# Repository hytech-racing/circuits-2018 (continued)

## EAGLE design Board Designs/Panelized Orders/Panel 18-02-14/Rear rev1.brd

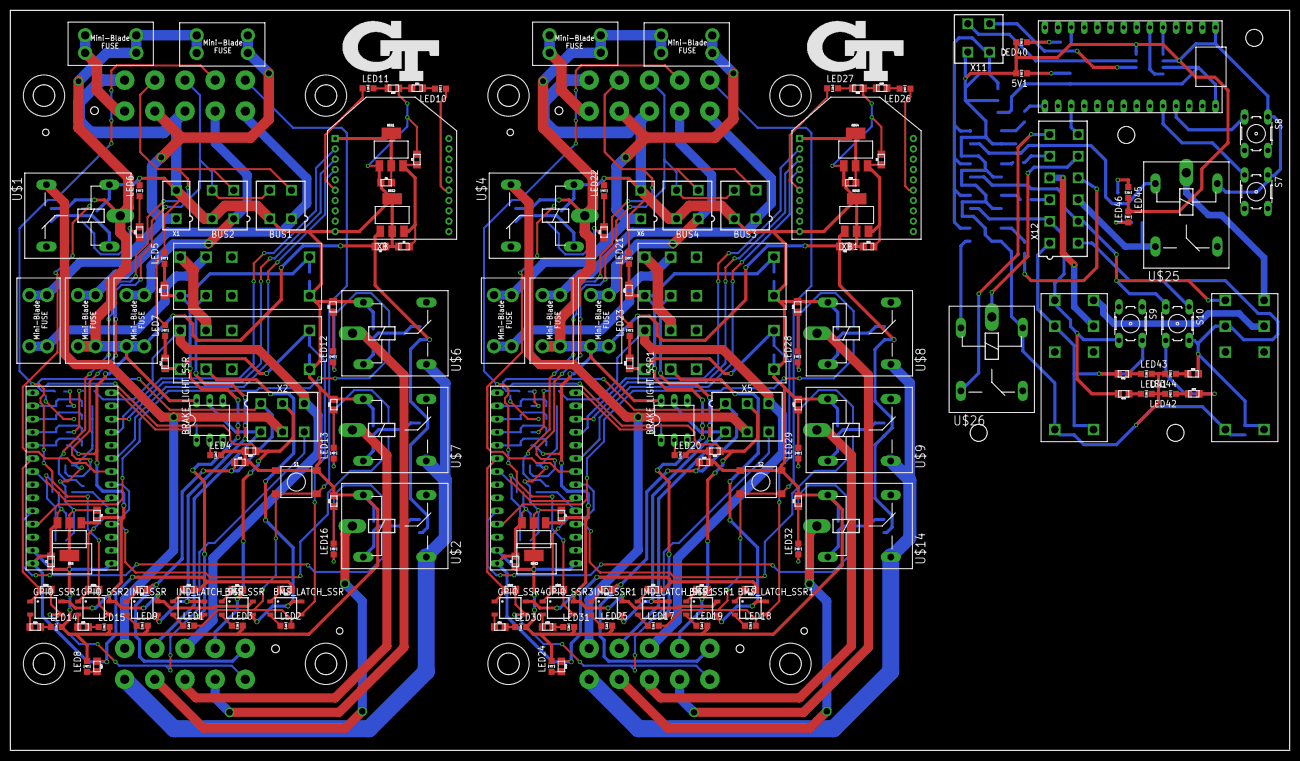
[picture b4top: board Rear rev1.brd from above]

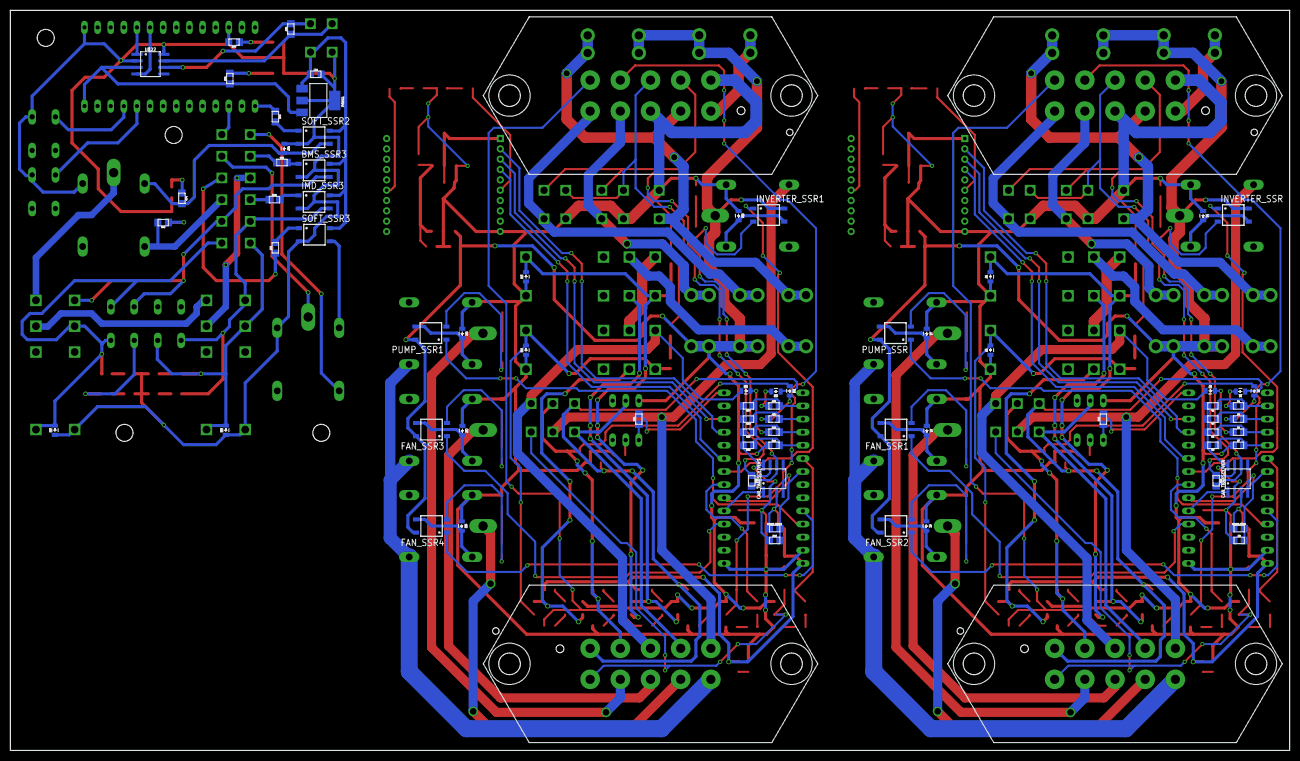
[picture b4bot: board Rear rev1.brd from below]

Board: 2 copper layers, 247.7 x 143.3 mm, 236 parts (75 on the bottom side), 203 nets.

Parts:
5V1: LED-805
5VREG1: SOT223
BMS_LATCH_SSR, BMS_LATCH_SSR1: CPC1002N; SOP04
BMS_SSR, BMS_SSR1, BMS_SSR3: CPC1002N; SOP04
BOARD_TEMP, BOARD_TEMP1: THERMISTOR_NCP210805; 0805
BRAKE_LIGHT_SSR, BRAKE_LIGHT_SSR1: SOLID_STATE_RELAY_VO14642AT; DIL06
BUS1, BUS2, BUS3, BUS4: CONNECTOR-4; MINIFIT_5566-4
C1, C5, C7, C11, C14: .22uF; 0805
C2, C6, C8, C12: .1uF; 0805
C3, C4, C9, C10: 1uF; 0805
CAN_TRANSCEIVER, CAN_TRANSCEIVER1: MCP2551; SOIC-08
D1, D2, D3, D4, D5, D6, D7, D8, D9, D10, D11, D12, D13, D14, D15, D16, D17, D18, D22, D23, D24: DIODE0805; 0805_D
FAN_SSR1, FAN_SSR2, FAN_SSR3, FAN_SSR4: CPC1002N; SOP04
FH_FUSE, FH_FUSE1: 8A; MINI-BLADE_FUSE_HOLDER
FSAE_FUSE, FSAE_FUSE1: 8A; MINI-BLADE_FUSE_HOLDER
FUSE_BUS_1, FUSE_BUS_2, FUSE_BUS_3, FUSE_BUS_4: 5A; MINI-BLADE_FUSE_HOLDER
GPIO_SSR1, GPIO_SSR2, GPIO_SSR3, GPIO_SSR4: CPC1002N; SOP04
IMD_LATCH_SSR, IMD_LATCH_SSR1: CPC1002N; SOP04
IMD_SHUTDOWN, IMD_SHUTDOWN1, IMD_SHUTDOWN2, IMD_SHUTDOWN3: G2RL-2-DC12; G2RL-2
IMD_SSR, IMD_SSR1, IMD_SSR3: CPC1002N; SOP04
INVERTER_SSR, INVERTER_SSR1: CPC1002N; SOP04
LED1, LED2, LED17, LED18: White; LED-805
LED3, LED7, LED11, LED19, LED23, LED27: Green; LED-805
LED4, LED6, LED10, LED12, LED13, LED14, LED15, LED16, LED20, LED22, LED26, LED28, LED29, LED30, LED31, LED32: Red; LED-805
LED5, LED9, LED21, LED25: Yellow; LED-805
LED8, LED24: Purple; LED-805
LED40, LED41, LED42, LED43, LED44, LED45, LED46: LED-805
PUMP_SSR, PUMP_SSR1: CPC1002N; SOP04
R1, R3, R5, R7, R25, R37, R39, R41: 43k; 0805
R2, R4, R6, R8, R36, R38, R40, R42: 12k; 0805
R9, R19, R43, R46: 10k; 0805
R10, R11, R16, R26, R29, R30, R31, R44, R54, R55: 43; 0805
R12, R13, R23, R24, R27, R28, R32, R33, R51, R52, R53, R56: 33; 0805
R14, R17, R21, R34, R45, R49: 820; 0805
R15, R35, R78: 120; 0805
R18, R47: 2.2k; 0805
R20, R48: 270; 0805
R22, R50: 100; 0805
R70, R71, R72, R73, R74, R75, R76, R77, R79, R80, R81, R82: 0805
REG, REG2, REG3, REG5: 5V; SOT223
REG1, REG4: TLV1117LV33; SOT223
S1, S2: TACTILE_SWITCH_SMD_6.2MM_TALL
S7, S8, S9, S10: B3F-10XX
SHUTDWN_FUSE, SHUTDWN_FUSE1: 5A; MINI-BLADE_FUSE_HOLDER
SOFT_SSR2, SOFT_SSR3: CPC1002N; SOP04
U$1, U$2, U$4, U$6, U$7, U$8, U$9, U$14, U$25, U$26: G5LE; ZF112
U$3, U$5, U$21: TEENSY_3.2_SIMPLE
U$10, U$11, U$12, U$13: JUMPER; 0805
U$22: MCP2551; SOIC-08
U$23, U$24: G2RL-2-DC12; G2RL-2
X1, X6: CONNECTOR-2; MINIFIT_5566-2
X2, X5: CONNECTOR-6; MINIFIT_5566-6
X3, X4, X7, X8: CONNECTOR-10MX150L_VERTICAL-10; MX150L_VERTICAL-10
X11: CONNECTOR-4; MINIFIT_5566-4
X12: CONNECTOR-12; MINIFIT_5566-12
XB, XB1: XBEE

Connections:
12VSUPPLY_BRB: FH_FUSE.R1, FH_FUSE.R2, SHUTDWN_FUSE.R1, SHUTDWN_FUSE.R2, X1.1, X4.2
12VSUPPLY_BRB1: FH_FUSE1.R1, FH_FUSE1.R2, SHUTDWN_FUSE1.R1, SHUTDWN_FUSE1.R2, X6.1, X8.2
12VSUPPLY_FSAE: FSAE_FUSE.R1, FSAE_FUSE.R2, X4.1
12VSUPPLY_FSAE1: FSAE_FUSE1.R1, FSAE_FUSE1.R2, X8.1
12VSUPPLY_READ: R7.2, R8.1, U$3.A3
12VSUPPLY_READ1: R41.2, R42.1, U$5.A3
12V_F1: BUS1.1, FUSE_BUS_1.R1, FUSE_BUS_1.R2, X4.5
12V_F2: BUS2.1, FUSE_BUS_2.R1, FUSE_BUS_2.R2, X4.4
12V_F3: BUS3.1, FUSE_BUS_3.R1, FUSE_BUS_3.R2, X8.5
12V_F4: BUS4.1, FUSE_BUS_4.R1, FUSE_BUS_4.R2, X8.4
+5V: BOARD_TEMP.1, C2.2, CAN_TRANSCEIVER.3, R12.2, R13.1, R20.1, REG.3, U$3.VIN
+5V1: BOARD_TEMP1.1, C8.2, CAN_TRANSCEIVER1.3, R32.2, R33.1, R48.1, REG3.3, U$5.VIN
+5V3: 5VREG1.3, R71.1, U$21.VIN, U$22.3
+12V: BMS_SSR.4, BRAKE_LIGHT_SSR.6, C1.2, C5.2, FAN_SSR1.4, FAN_SSR2.4, FH_FUSE.L1, FH_FUSE.L2, FSAE_FUSE.L1, FSAE_FUSE.L2, FUSE_BUS_1.L1, FUSE_BUS_1.L2, FUSE_BUS_2.L1, FUSE_BUS_2.L2, GPIO_SSR1.4, GPIO_SSR2.4, IMD_SSR.4, INVERTER_SSR.4, PUMP_SSR.4, R7.1, REG.1, REG2.1, U$1.P
+12V1: BMS_SSR1.4, BRAKE_LIGHT_SSR1.6, C7.2, C11.2, FAN_SSR3.4, FAN_SSR4.4, FH_FUSE1.L1, FH_FUSE1.L2, FSAE_FUSE1.L1, FSAE_FUSE1.L2, FUSE_BUS_3.L1, FUSE_BUS_3.L2, FUSE_BUS_4.L1, FUSE_BUS_4.L2, GPIO_SSR3.4, GPIO_SSR4.4, IMD_SSR1.4, INVERTER_SSR1.4, PUMP_SSR1.4, R41.1, REG3.1, REG5.1, U$4.P
+12V3: 5VREG1.1, BMS_SSR3.4, C14.1, IMD_SSR3.4, SOFT_SSR2.4, SOFT_SSR3.4, X11.1
BMS_12V1: BMS_SSR3.3, R77.2, S10.3, S10.4, U$24.4, X12.8
BMS_COIL_PWR: BMS_LATCH_SSR.3, D5.C, IMD_SHUTDOWN1.4, IMD_SHUTDOWN1.COIL-, R17.1
BMS_COIL_PWR1: BMS_LATCH_SSR1.3, D14.C, IMD_SHUTDOWN3.4, IMD_SHUTDOWN3.COIL-, R45.1
BMS_INRLK1: R81.1, X12.10
BMS_OK: D2.A, R11.2, R19.1, X2.2, X3.2
BMS_OK1: D11.A, R31.2, R46.1, X5.2, X7.2
BMS_OK3: D23.C, R73.2, S10.1, S10.2, U$24.3, U$24.COIL-, X12.7
BMS_OK_READ: R3.2, R4.1, U$3.A1
BMS_OK_READ1: R37.2, R38.1, U$5.A1
BMS_PWR_STEP: BMS_LATCH_SSR.4, BMS_SSR.3, IMD_SHUTDOWN1.3
BMS_PWR_STEP1: BMS_LATCH_SSR1.4, BMS_SSR1.3, IMD_SHUTDOWN3.3
BRAKE_LIGHT: BRAKE_LIGHT_SSR.5, X2.4, X3.4
BRAKE_LIGHT1: BRAKE_LIGHT_SSR1.5, X5.4, X7.4
BRAKE_LIGHT_CTRL: R10.2, U$3.D12
BRAKE_LIGHT_CTRL1: R26.2, U$5.D12
BTN_X1: S8.3, U$21.A9
BTN_Y1: S7.3, U$21.A8
CANH: BUS1.4, BUS2.4, CAN_TRANSCEIVER.7, R15.1, X4.8
CANH1: BUS3.4, BUS4.4, CAN_TRANSCEIVER1.7, R35.1, X8.8
CANH3: R78.1, U$22.7, X11.4
CANL: BUS1.3, BUS2.3, CAN_TRANSCEIVER.6, R15.2, X4.7
CANL1: BUS3.3, BUS4.3, CAN_TRANSCEIVER1.6, R35.2, X8.7
CANL3: R78.2, U$22.6, X11.3
CANRX1: U$21.D4(CANRX), U$22.4
CANTX1: U$21.D3(CANTX), U$22.1
FAN1-: U$7.P, X3.8
FAN1-1: U$9.P, X7.8
FAN2-: U$2.P, X3.9
FAN2-1: U$14.P, X7.9
GND: BUS1.2, BUS2.2, C1.1, C2.1, C3.2, C4.1, C5.1, C6.1, CAN_TRANSCEIVER.2, CAN_TRANSCEIVER.8, D4.A, D5.A, D6.A, D7.A, D8.A, D9.A, IMD_SHUTDOWN.COIL+, IMD_SHUTDOWN1.COIL+, LED3.C, LED4.C, LED5.C, LED6.C, LED7.C, LED8.C, LED9.C, LED14.C, LED15.C, R2.2, R4.2, R6.2, R8.2, R9.1, R18.2, R19.2, R22.1, R23.1, R24.2, R27.2, R28.2, REG.2, REG.4, REG1.1, REG2.2, REG2.4, S1.B1, S1.B2, U$1.2, U$2.1, U$3.AGND, U$3.GND, U$6.1, U$7.1, X1.2, X4.3, X4.6, XB.10
GND1: U$2.S, U$6.S, U$7.S, X3.10
GND2: BUS3.2, BUS4.2, C7.1, C8.1, C9.2, C10.1, C11.1, C12.1, CAN_TRANSCEIVER1.2, CAN_TRANSCEIVER1.8, D13.A, D14.A, D15.A, D16.A, D17.A, D18.A, IMD_SHUTDOWN2.COIL+, IMD_SHUTDOWN3.COIL+, LED19.C, LED20.C, LED21.C, LED22.C, LED23.C, LED24.C, LED25.C, LED30.C, LED31.C, R36.2, R38.2, R40.2, R42.2, R43.1, R46.2, R47.2, R50.1, R51.1, R52.2, R53.2, R56.2, REG3.2, REG3.4, REG4.1, REG5.2, REG5.4, S2.B1, S2.B2, U$4.2, U$5.AGND, U$5.GND, U$8.1, U$9.1, U$14.1, X6.2, X8.3, X8.6, XB1.10
GND3: U$8.S, U$9.S, U$14.S, X7.10
GND5: 5V1.C, 5VREG1.2, 5VREG1.4, BMS_SSR3.2, C14.2, D22.A, D23.A, D24.A, IMD_SSR3.2, LED40.C, LED41.C, LED42.C, LED43.C, LED44.C, LED45.C, LED46.C, S7.1, S8.1, SOFT_SSR2.2, SOFT_SSR3.2, U$21.GND, U$22.2, U$22.8, U$23.COIL+, U$24.COIL+, U$25.1, U$26.1, X11.2
GPIO1: U$21.A1, X12.12
GPIO_1: GPIO_SSR1.3, U$10.2, X2.6, X3.6
GPIO_2: GPIO_SSR2.3, U$11.2, X4.9
GPIO_3: GPIO_SSR3.3, U$13.2, X8.9
GPIO_4: GPIO_SSR4.3, U$12.2, X5.6, X7.6
GPIO_CTRL1: GPIO_SSR1.1, U$3.A4, U$10.1
GPIO_CTRL2: GPIO_SSR2.1, U$3.D5, U$11.1
GPIO_CTRL3: GPIO_SSR3.1, U$5.D5, U$13.1
GPIO_CTRL4: GPIO_SSR4.1, U$5.A4, U$12.1
IMD_12V1: IMD_SSR3.3, R76.2, S9.3, S9.4, U$23.4, X12.2
IMD_COIL_PWR: D6.C, IMD_LATCH_SSR.3, IMD_SHUTDOWN.4, IMD_SHUTDOWN.COIL-, R14.1
IMD_COIL_PWR1: D15.C, IMD_LATCH_SSR1.3, IMD_SHUTDOWN2.4, IMD_SHUTDOWN2.COIL-, R34.1
IMD_OK1: D22.C, R72.2, S9.1, S9.2, U$23.3, U$23.COIL-, X12.1
IMD_PWR_STEP: IMD_LATCH_SSR.4, IMD_SHUTDOWN.3, IMD_SSR.3
IMD_PWR_STEP1: IMD_LATCH_SSR1.4, IMD_SHUTDOWN2.3, IMD_SSR1.3
INVERTER_CTRL: INVERTER_SSR.1, U$3.D6
INVERTER_CTRL1: INVERTER_SSR1.1, U$5.D6
INVERTER_SUPPLY: U$1.S, X2.5, X3.5
INVERTER_SUPPLY1: U$4.S, X5.5, X7.5
LATCH_EXT_BUTTON: LED1.C, LED2.C, S1.A1, S1.A2, X4.10
LATCH_EXT_BUTTON1: LED17.C, LED18.C, S2.A1, S2.A2, X8.10
unnamed: IMD_LATCH_SSR.2, LED1.A
unnamed: CAN_TRANSCEIVER.4, U$3.D4(CANRX)
unnamed: CAN_TRANSCEIVER.1, U$3.D3(CANTX)
unnamed: D7.C, PUMP_SSR.3, U$6.2
unnamed: IMD_LATCH_SSR.1, R12.1
unnamed: GPIO_SSR1.2, R29.1
unnamed: BRAKE_LIGHT_SSR.2, LED4.A
unnamed: GPIO_SSR2.2, R30.1
unnamed: BMS_SSR.2, LED3.A
unnamed: LED10.A, XB.15
unnamed: LED10.C, R22.2
unnamed: BMS_LATCH_SSR.1, R13.2
unnamed: LED14.A, R29.2
unnamed: LED15.A, R30.2
unnamed: BOARD_TEMP.2, R9.2, U$3.A5
unnamed: BMS_LATCH_SSR.2, LED2.A
unnamed: BRAKE_LIGHT_SSR.1, R10.1
unnamed: BMS_SSR.1, R11.1
unnamed: LED5.A, R14.2
unnamed: D8.C, FAN_SSR1.3, U$7.2
unnamed: D9.C, FAN_SSR2.3, U$2.2
unnamed: D1.C, R1.1
unnamed: D2.C, R3.1
unnamed: D3.C, R5.1
unnamed: LED11.A, XB.6
unnamed: D4.C, INVERTER_SSR.3, U$1.1
unnamed: INVERTER_SSR.2, R16.1
unnamed: LED6.A, R16.2
unnamed: LED8.A, R20.2
unnamed: LED16.C, R24.1
unnamed: IMD_SSR.1, R21.2
unnamed: LED7.A, R17.2
unnamed: LED11.C, R23.2
unnamed: IMD_SSR.2, LED9.A
unnamed: C3.1, C6.2, REG1.3, REG2.3
unnamed: LED13.C, R28.1
unnamed: LED12.C, R27.1
unnamed: LED12.A, PUMP_SSR.2
unnamed: FAN_SSR2.2, LED16.A
unnamed: CAN_TRANSCEIVER1.4, U$5.D4(CANRX)
unnamed: CAN_TRANSCEIVER1.1, U$5.D3(CANTX)
unnamed: FAN_SSR1.2, LED13.A
unnamed: BOARD_TEMP1.2, R43.2, U$5.A5
unnamed: IMD_LATCH_SSR1.2, LED17.A
unnamed: BMS_SSR1.2, LED19.A
unnamed: BMS_SSR1.1, R31.1
unnamed: BRAKE_LIGHT_SSR1.2, LED20.A
unnamed: BRAKE_LIGHT_SSR1.1, R26.1
unnamed: LED21.A, R34.2
unnamed: D10.C, R25.1
unnamed: D11.C, R37.1
unnamed: D12.C, R39.1
unnamed: D13.C, INVERTER_SSR1.3, U$4.1
unnamed: INVERTER_SSR1.2, R44.1
unnamed: LED22.A, R44.2
unnamed: IMD_LATCH_SSR1.1, R32.1
unnamed: BMS_LATCH_SSR1.2, LED18.A
unnamed: BMS_LATCH_SSR1.1, R33.2
unnamed: LED23.A, R45.2
unnamed: LED24.A, R48.2
unnamed: IMD_SSR1.2, LED25.A
unnamed: IMD_SSR1.1, R49.2
unnamed: LED26.A, XB1.15
unnamed: LED26.C, R50.2
unnamed: LED27.C, R51.2
unnamed: LED27.A, XB1.6
unnamed: C9.1, C12.2, REG4.3, REG5.3
unnamed: D16.C, PUMP_SSR1.3, U$8.2
unnamed: D17.C, FAN_SSR3.3, U$9.2
unnamed: LED29.C, R53.1
unnamed: LED28.C, R52.1
unnamed: LED28.A, PUMP_SSR1.2
unnamed: FAN_SSR3.2, LED29.A
unnamed: GPIO_SSR4.2, R54.1
unnamed: GPIO_SSR3.2, R55.1
unnamed: LED30.A, R54.2
unnamed: LED31.A, R55.2
unnamed: D18.C, FAN_SSR4.3, U$14.2
unnamed: LED32.C, R56.1
unnamed: FAN_SSR4.2, LED32.A
unnamed: LED41.A, R76.1
unnamed: LED43.A, R72.1
unnamed: LED44.A, R73.1
unnamed: LED45.A, R74.1
unnamed: LED46.A, R75.1
unnamed: LED42.A, R77.1
unnamed: SOFT_SSR3.3, U$26.2
unnamed: LED40.A, R70.1
unnamed: R70.2, U$21.D10(TX2)
unnamed: 5V1.A, R71.2
unnamed: U$26.P, X12.11
unnamed: U$26.S, X12.6
unnamed: IMD_SSR3.1, R79.2
unnamed: BMS_SSR3.1, R80.2
unnamed: R79.1, X12.3
unnamed: R80.1, X12.5
unnamed: R81.2, SOFT_SSR3.1
unnamed: R82.1, U$21.D13
OKHS: D1.A, R18.1, R21.1, X2.1, X3.1
OKHS1: D10.A, R47.1, R49.1, X5.1, X7.1
OKHS_READ: R1.2, R2.1, U$3.A0
OKHS_READ1: R25.2, R36.1, U$5.A0
PUMP1-: U$6.P, X3.7
PUMP1-1: U$8.P, X7.7
RELAY_CTRL1: PUMP_SSR.1, U$3.A9
RELAY_CTRL2: FAN_SSR1.1, U$3.D2
RELAY_CTRL3: FAN_SSR2.1, U$3.A8
RELAY_CTRL4: FAN_SSR3.1, U$5.D2
RELAY_CTRL5: PUMP_SSR1.1, U$5.A9
RELAY_CTRL6: FAN_SSR4.1, U$5.A8
SHUTDOWN_A: IMD_SHUTDOWN.6, SHUTDWN_FUSE.L1, SHUTDWN_FUSE.L2
SHUTDOWN_A1: IMD_SHUTDOWN2.6, SHUTDWN_FUSE1.L1, SHUTDWN_FUSE1.L2
SHUTDOWN_B: IMD_SHUTDOWN.5, IMD_SHUTDOWN1.6
SHUTDOWN_B1: IMD_SHUTDOWN2.5, IMD_SHUTDOWN3.6
SHUTDOWN_C: D3.A, IMD_SHUTDOWN1.5, X2.3, X3.3
SHUTDOWN_C1: D12.A, IMD_SHUTDOWN3.5, X5.3, X7.3
SHUTDOWN_IN1: U$23.6, X12.4
SHUTDOWN_IN_A1: U$23.5, U$24.6
SHUTDOWN_IN_B1: U$24.5, U$25.P
SHUTDOWN_OUT1: R75.2, U$25.S, X12.9
SHUTDOWN_OUT_READ: R5.2, R6.1, U$3.A2
SHUTDOWN_OUT_READ1: R39.2, R40.1, U$5.A2
SW_KILL1: R82.2, SOFT_SSR2.1
SW_KILL_RELAY1: D24.C, R74.2, SOFT_SSR2.3, U$25.2
VCC: C4.2, REG1.2, REG1.4, XB.1
VCC1: C10.2, REG4.2, REG4.4, XB1.1
XB1: U$5.D7(RX3), XB1.4
XB8: U$3.D7(RX3), XB.4
XBDI: U$3.D10(TX2), XB.3
XBDI1: U$5.D10(TX2), XB1.3
XBDO: U$3.D9(RX2), XB.2
XBDO1: U$5.D9(RX2), XB1.2

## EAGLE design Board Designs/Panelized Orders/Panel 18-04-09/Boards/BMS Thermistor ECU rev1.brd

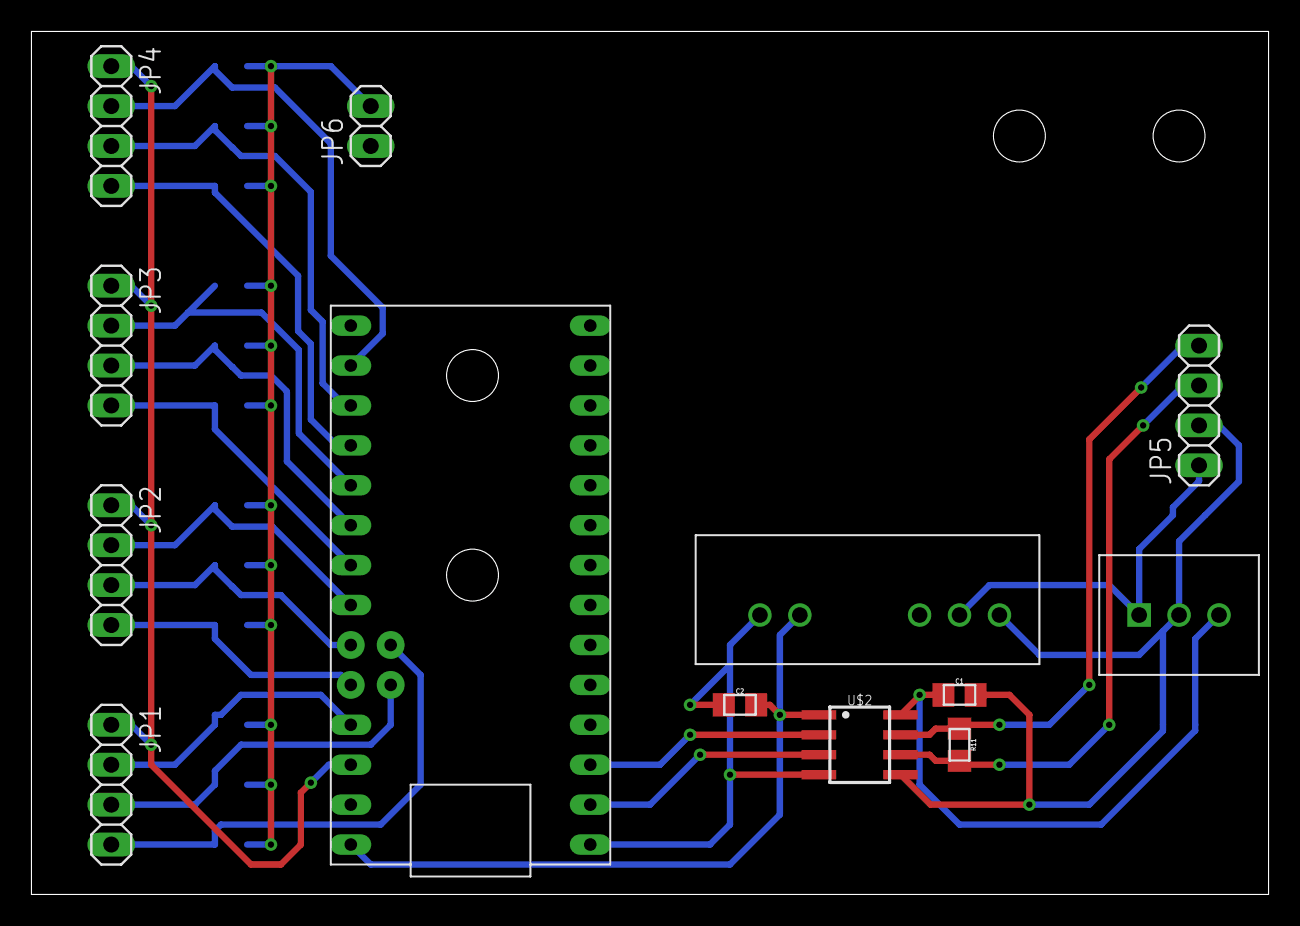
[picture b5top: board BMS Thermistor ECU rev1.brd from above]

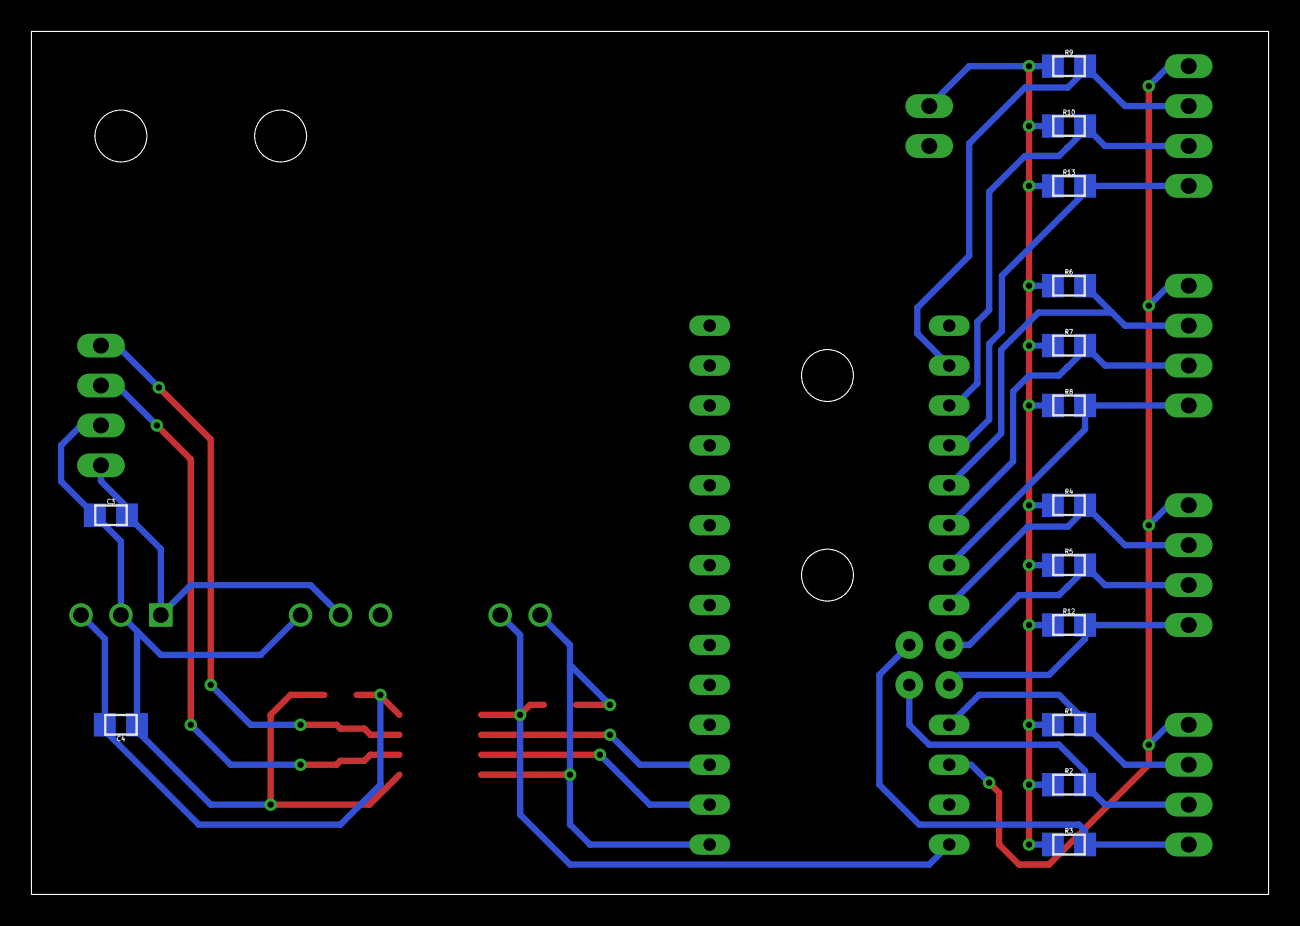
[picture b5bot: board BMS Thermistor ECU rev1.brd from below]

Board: 2 copper layers, 78.7 x 54.9 mm, 27 parts (14 on the bottom side), 23 nets.

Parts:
C1, C2, C4: 0.1u; 0805
C3: 0.33u; 0805
IC1: TO-220-SPACED
JP1, JP2, JP3, JP4, JP5: 1X04
JP6: M02; 1X02
R1, R2, R3, R4, R5, R6, R7, R8, R9, R10, R12, R13: 0805
R11: 120; 0805
U$1: TEENSY_3.2_12ANALOG
U$2: ISO1050CAN; SOIC-08
U$3: NCS1S1205SC-12V-5VCONVERTER; DCDC-CONVERTER

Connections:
3.3V: JP1.1, JP2.1, JP3.1, JP4.1, U$1.3.3V
unnamed: C1.2, C3.1, C4.1, IC1.2, JP5.2, U$2.5, U$3.-VIN
unnamed: JP3.3, R7.2, U$1.A4
unnamed: JP3.4, R8.2, U$1.A5
unnamed: C3.2, IC1.1, JP5.1, U$3.+VIN
unnamed: C1.1, C4.2, IC1.3, U$2.8
unnamed: JP5.4, R11.1, U$2.7
unnamed: JP5.3, R11.2, U$2.6
unnamed: U$1.D0(RX1), U$2.3
unnamed: U$1.D1(TX1), U$2.2
unnamed: C2.2, U$1.VIN, U$2.1, U$3.+VOUT
unnamed: C2.1, U$1.GND, U$2.4, U$3.-VOUT
unnamed: JP2.4, R12.2, U$1.A8
unnamed: JP4.4, R13.2, U$1.A2
THERM1: JP1.2, R1.2, U$1.A9
THERM2: JP1.3, R2.2, U$1.A10
THERM3: JP1.4, R3.2, U$1.A11
THERM4: JP2.2, R4.2, U$1.A6
THERM5: JP2.3, R5.2, U$1.A7
THERM6: JP3.2, R6.2, U$1.A3
THERM9: JP4.2, R9.2, U$1.A0
THERM10: JP4.3, R10.2, U$1.A1
TS_GND: JP6.2, R1.1, R2.1, R3.1, R4.1, R5.1, R6.1, R7.1, R8.1, R9.1, R10.1, R12.1, R13.1
